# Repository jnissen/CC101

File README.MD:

*Deutsch | [English](README.en.md)*

# Peerhof-Uni CC1101

KiCad-Projekt für eine kompakte Trägerplatine, die einen **ESP8266 (Wemos D1 Mini)** mit einem **CC1101 Sub-GHz-Funkmodul** (z. B. 433/868 MHz) kombiniert. Die Platine dient als universelles Funk-Gateway bzw. -Sender/Empfänger und lässt sich z. B. zur Anbindung von 433-MHz-Sensoren, Aktoren oder Smarthome-Komponenten an WLAN nutzen.

## Projektvarianten

Das Repository enthält zwei Varianten desselben Designs:

- **[CC1101-ESP-8266-D1-Mini](CC1101-ESP-8266-D1-Mini/)** – *Light-Version*  
  Schlanke Variante ohne eigene Spannungsversorgung. Versorgung erfolgt direkt über den USB-Anschluss bzw. den 5-V-Pin des D1 Mini. Ideal, wenn bereits eine stabile 5-V-Quelle vorhanden ist.

- **[CC1101-ESP8266-D1-Mini-With Power Supply](CC1101-ESP8266-D1-Mini-With%20Power%20Supply/)** – *Variante mit Netzteil*  
  Erweiterte Version mit zusätzlicher Bordspannungsversorgung für den autarken Betrieb (z. B. direkt aus einer höheren DC-Eingangsspannung).

## Funktionen / Merkmale

- ESP8266 auf Basis des Wemos D1 Mini (WLAN, einfache Programmierung über USB).
- CC1101-Funkmodul für Sub-GHz-Kommunikation (ASK/OOK, FSK, GFSK, MSK).
- Herausgeführte Stiftleisten:
  - `J2`: D4 / GND / 5 V
  - `J3`: D3 / D1 / GND / 5 V
  - `J4`: RX / TX / GND / 3,3 V (UART)
- Pad-Feld `AE1` für eine externe Antenne / Helix-Antenne.
- Status-LED `D1`.
- Zweilagiges PCB-Design, fertige Gerber-Daten liegen jeweils im Ordner `gerber/`.

## Verzeichnisstruktur

```
CC1101-ESP-8266-D1-Mini/                  KiCad-Projekt (Light)
CC1101-ESP8266-D1-Mini-With Power Supply/ KiCad-Projekt (mit Netzteil)
└── gerber/                               Fertigungsdaten (Gerber + Bohrdatei)
```

## Verwendung

1. Projekt in **KiCad** öffnen (`.kicad_pro`).
2. Schaltplan (`.kicad_sch`) und Layout (`.kicad_pcb`) prüfen bzw. anpassen.
3. Gerber-Daten aus dem jeweiligen `gerber/`-Ordner an einen PCB-Hersteller übermitteln.
4. Bestücken, ESP8266 mit gewünschter Firmware flashen (z. B. ESPHome, Tasmota mit CC1101-Patch, eigene Arduino-Skizze) und an SPI-Pins des D1 Mini anschließen.

## Bezugsquellen

- CC1101-Funkmodul (Amazon, Affiliate-Link): <https://amzn.to/4uQriL0>
- Wemos D1 Mini (ESP8266) (Amazon, Affiliate-Link): <https://amzn.to/4tIXEXa>

## Lizenz

Dieses Projekt steht unter der **CERN-OHL-W-2.0** Lizenz: <https://ohwr.org/cern_ohl_w_v2.txt>

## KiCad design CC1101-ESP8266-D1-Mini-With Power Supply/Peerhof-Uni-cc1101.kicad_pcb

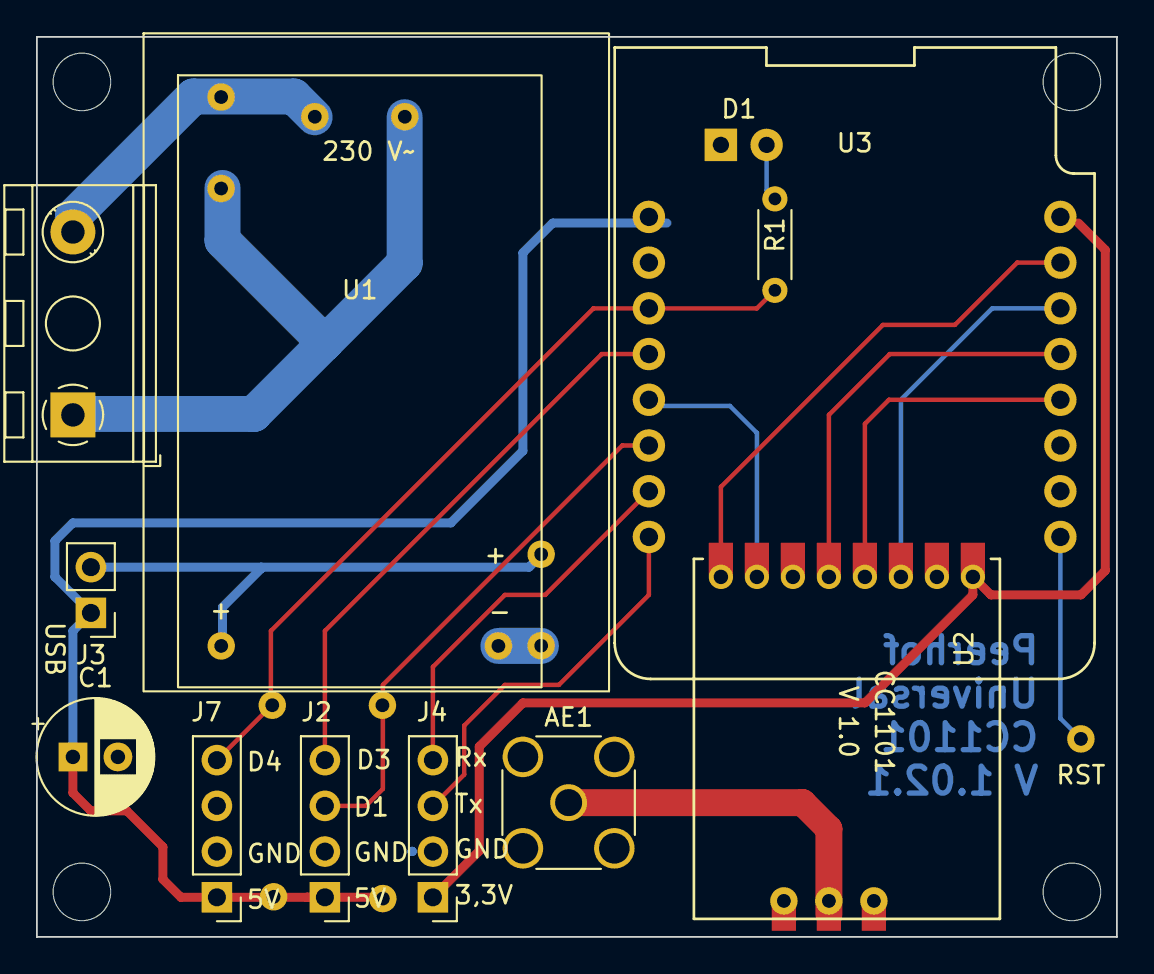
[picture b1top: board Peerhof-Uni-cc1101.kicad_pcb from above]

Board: 2 copper layers, 60.0 x 50.0 mm, 12 parts (1 on the bottom side), 18 nets.

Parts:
AE1: Antenna_Shield; SMA_Wurth_60312002114503_Vertical
C1: C_Polarized_Small; CP_Radial_D6.3mm_P2.50mm
D1: LED; LED_D1.8mm_W1.8mm_H2.4mm_Horizontal_O3.81mm_Z1.6mm
J1: Screw_Terminal_01x02; TerminalBlock_RND_205-00241_1x02_P10.16mm_Horizontal
J2: ToF(D1/D2); PinHeader_1x04_P2.54mm_Vertical
J3: Conn_01x02_Male; PinHeader_1x02_P2.54mm_Vertical
J4: Rx/Tx; PinHeader_1x04_P2.54mm_Vertical
J7: DHT11; PinHeader_1x04_P2.54mm_Vertical
R1: 470K; R_Axial_DIN0204_L3.6mm_D1.6mm_P5.08mm_Horizontal
U1: AC-05-3; HLK-PM01-AC-05-3
U2: CC1101
U3: WeMos_D1_mini; wemos-d1-mini-with-pin-header-and-connector

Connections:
+3.3V: J4.1, U2.1 (VCC), U3.8 (3.3V)
+5V: C1.1, J2.1, J3.1, J7.1, U3.9 (5V)
D1: J2.3, U3.14 (D1)
D2: U2.7 (GDO0), U3.13 (D2)
D3: J2.4, U3.12 (D3)
D4: J7.4, R1.2, U3.11 (D4)
D5: U2.4 (SCLK), U3.4 (D5)
D6: U2.5 (MISO), U3.5 (D6)
D7: U2.3 (MOSI), U3.6 (D7)
D8: U2.8 (CSN), U3.7 (D8)
GND: AE1.2 (Shield), C1.2, D1.1 (K), J2.2, J4.2, J7.2, U1.5 (-V), U2.2 (GND), U2.9 (GND), U2.11 (GND), U3.10 (GND)
unnamed: AE1.1 (A), U2.10 (Antenna)
unnamed: D1.2 (A), R1.1
unnamed: J1.1, U1.2 (N)
unnamed: J1.2, U1.1 (L)
unnamed: J3.2, U1.4 (+V)
Rx: J4.4, U3.15 (Rx)
Tx: J4.3, U3.16 (Tx)

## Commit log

2026-05-19 Initial PCB V 1.02.1
2026-05-19 Kicad Version 10.0
2026-05-19 with power Supply Project
2026-05-19 Switch project license to CERN-OHL-W
    Replaces the public domain Unlicense with the CERN Open Hardware Licence v2 - Weakly Reciprocal. This change promotes collaboration and ensures derivative works of the hardware designs remain open un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
2026-05-19 Readme.md
2026-05-19 chore: Leere Code-Änderungen ohne spezifische Anpassungen entfernt
2026-05-19 docs: Bild-Tag im README aktualisiert für bessere Darstellung
2026-05-19 docs: Leerzeile im README hinzugefügt für bessere Lesbarkeit
2026-05-19 docs: README aktualisiert mit Projektbeschreibung und Funktionen
2026-05-19 chore: Leere Code-Änderungen ohne spezifische Anpassungen
2026-05-19 chore: Leere Code-Änderungen ohne spezifische Anpassungen hinzugefügt
2026-05-19 docs: README aktualisiert und englische Übersetzung hinzugefügt
2026-05-19 docs: Bezugsquellen für CC1101 und Wemos D1 Mini im README hinzugefügt
